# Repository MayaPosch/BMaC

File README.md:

# Building Monitoring and Control 

The Building Monitoring and Control (**BMaC**) system consists out multiple components which all work together to allow one to monitor and control conditions within a building.

Communication between these components is performed over MQTT, requiring the use of an (existing) MQTT broker. An Influx database instance is used to register sensor data, allowing this data to be used by other services. An existing InfluxDB instance can be used, or a new one created for the BMaC system.

A graphical overview:

## Components

* Command & Control server
* Command & Control client
* Control & Monitoring node
* AC control service
* OTA update service
* Influx-MQTT service

## Refactoring Notice ##

**Notice:** Be aware that the BMaC project is currently being refactored and will undergo a number of changes:

* ESP8266-based node firmware:
	- Auto-configuration using NyanSD service discovery.
	- Update & potentially remove unused modules.
* Merging of services:
	- The Command & Control server, AC & Influx-MQTT services are being merged into the 'Controller' service.
	- These old services will be retired after the merge completes.
* Web-based administration panel:
	- The new BMaC Controller server will provide a web-based interface for managing BMaC nodes and other parts of a BMaC installation.

### Command & Control server

This component (C&C server, or **CCS**) is used to register the configuration for individual nodes with. Each node can feature a different range of active sensors and actuators, which are enabled in the firmware at start-up of the node after they obtain their configuration from this server.

The C&C client is used to read out the current node configurations, update configurations and add new nodes.

### Command & Control client

This client (C&C client, or **CCC**) is based around a graphical user interface, which displays the map of the current building layout, along with the position of each node. By selecting a node, one can see its current configuration and update it.

After creating a new node or updating an existing one, the changed configuration can be saved on the C&C server or be sent directly to the node (useful for testing purposes).

### Control & Monitoring node

Also called **CMN**. In its current iteration these are ESP8266-based systems. Generally they are fitted into a wall- or ceiling-mounted enclosure using a custom board with the ability to mount temperature, CO2 and other sensors. They can also be in the form of a simple switch, in which case they are fitted into an electrical box, usually to replace a manual switch.

Each node runs the same firmware, yet can be configured via the CCS to only enable specific modules.

Current modules are:

* **Temperature/Humidity** - Uses the Bosch BME280 sensor to read temperature, humidity and air pressure.
* **CO2** - Uses the MH-Z19 and compatible (MH-Z14) CO2 sensor's serial interface to obtain PPM levels.
* **Jura** - Reads out current statistics on total number of coffee consumed for compatible Toptronic-based automatic coffee machines.
* **JuraTerm** - Allows for direct control of compatible Toptronic-based coffee machines using the serial protocol over MQTT.
* **Motion** - Uses compatible PIR motion sensors (e.g.  the HC-SR501) with 3.3V TTL output.
* **PWM** - Generates a PWM signal of variable duty, set to 1 KHz.
* **IO** - Uses the MCP23008 GPIO expander to increase the number of digital GPIO pins.
* **Switch** - Uses an external 2-coil latching relay to switch an input between two possible outputs and read the current setting back.

### AC control service

The AC control service (accontrol, or **ACCS**) builds upon the CCS, CMNs as well as the data stored in the Influx database in order to control the room temperature using installed Fan Coil Units (**FCUs**), along with the valves in the system (both 2- and 4-pipe FCUs).

It provides a HTTP REST API along with a simple browser-based interface using which one can set the target temperature for a particular node and read out the current temperature.

### OTA update service

The OTA update service (**OTAU**) works together with the CMN firmware to allow a CMN to update itself with a new firmware image. After the CMN receives an update trigger via its maintenance interface, it contacts a hard-coded HTTP URI to obtain the new firmware image.

The OTAU currently is a simple browser-based script using which CMNs can be added using their UID (MAC address) along with the name of the firmware image they should be downloading. When the CMN contacts the OTAU running inside a webserver, the OTAU selects the appropriate firmware image and sends it to the CMN.

### Influx-MQTT service

The Influx-MQTT service (**IMS**) can be configured to listen on a number of MQTT topics (sensor readings) and write those to a time series in the InfluxDB instance using its HTTP(S) line protocol.

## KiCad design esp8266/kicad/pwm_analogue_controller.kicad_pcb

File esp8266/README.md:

# Command & Control node

Also called **CMN**. In its current iteration these are ESP8266-based systems. Generally they are fitted into a wall- or ceiling-mounted enclosure using a custom board with the ability to mount temperature, CO2 and other sensors. They can also be in the form of a simple switch, in which case they are fitted into an electrical box, usually to replace a manual switch.

Each node runs the same firmware, yet can be configured via the CCS (Command & Control Server) to only enable specific modules.

Current modules are:

- **Temperature/Humidity** - Uses the Bosch BME280 sensor to read temperature, humidity and air pressure.
- **CO2** - Uses the MH-Z19 and compatible (MH-Z14) CO2 sensor's serial interface to obtain PPM levels.
- **Jura** - Reads out current statistics on total number of coffee consumed for compatible Toptronic-based automatic coffee machines.
- **JuraTerm** - Allows for direct control of compatible Toptronic-based coffee machines using the serial protocol over MQTT, terminal-style.
- **Motion** - Uses compatible PIR motion sensors (e.g.  the HC-SR501) with 3.3V TTL output.
- **PWM** - Generates a PWM signal of variable duty, set to 1 KHz.
- **IO** - Uses the MCP23008 GPIO expander to increase the number of digital GPIO pins.
- **Switch** - Uses an external 2-coil latching relay to switch an input between two possible outputs and read the current setting back.

## Usage ##

The firmware is designed to require minimal configuration. Other than the necessity of adding a file with the WiFi credentials (`files/wifi_creds.txt`), the configuration of the MQTT broker and OTA server is handled automatically, assuming the following dependencies are met:

- BMaC Controller server active on the network.
- MQTT broker active on the network.
- [NyanSD](https://github.com/MayaPosch/NyanSD "NyanSD") server running on port 11310 (UDP) for MQTT broker discovery.

With these services in place, the firmware will:

- Read the WiFi credentials from the `wifi_creds.txt` file.
- Connect to WiFi and broadcast a NyanSD message for the MQTT broker.
- Connect to the first MQTT broker.
- Send MQTT message to `cc/config` with its MAC as payload to obtain its configuration.

At this point the node should be active, and configurable via the BMaC Controller server.

## Building

This project is based on the Sming ESP8266 framework (https://github.com/SmingHub/Sming). As of writing the current 4.6 release is recommended.

After following the installation instructions for Sming in its documentation, to customise the BMaC firmware for the target WiFi network the credentials have to be added to the `files/` folder. This file has this format, with a question mark separating the SSID and password:

```
<WiFi SSID>?<WiFi password>
```

After this, there are a few more configuration options that can be set in the `component.mk` file of the project:

* Whether MQTT is run in secure (TLS) or insecure mode.

Note that when using TLS, one has to add the client certificate and key to the `files/` folder in binary format (not Base64):

* files/**esp8266.client.crt.binary**
* files/**esp8266.client.key.binary**

These files will then be added to the filesystem on the firmware image.

**NOTE:** Due to the limited RAM on the ESP8266, it is required to set the SSL fragment size option on the TLS termination point (MQTT broker or proxy, e.g. HAProxy). A fragment size of about 2 kB is recommended. The default 16 kB size (for TX & RX) will cause the ESP8266 to run out of memory during handshake and reset.

## PCB KiCad project ##

The KiCad project for the controller's PCB is found in the `kicad/` folder. From these the Gerber files can be generated for the PCBs.

The PCB is designed for the CamdenBoss CBRS01VWH enclosure (wall/ceiling-mount).

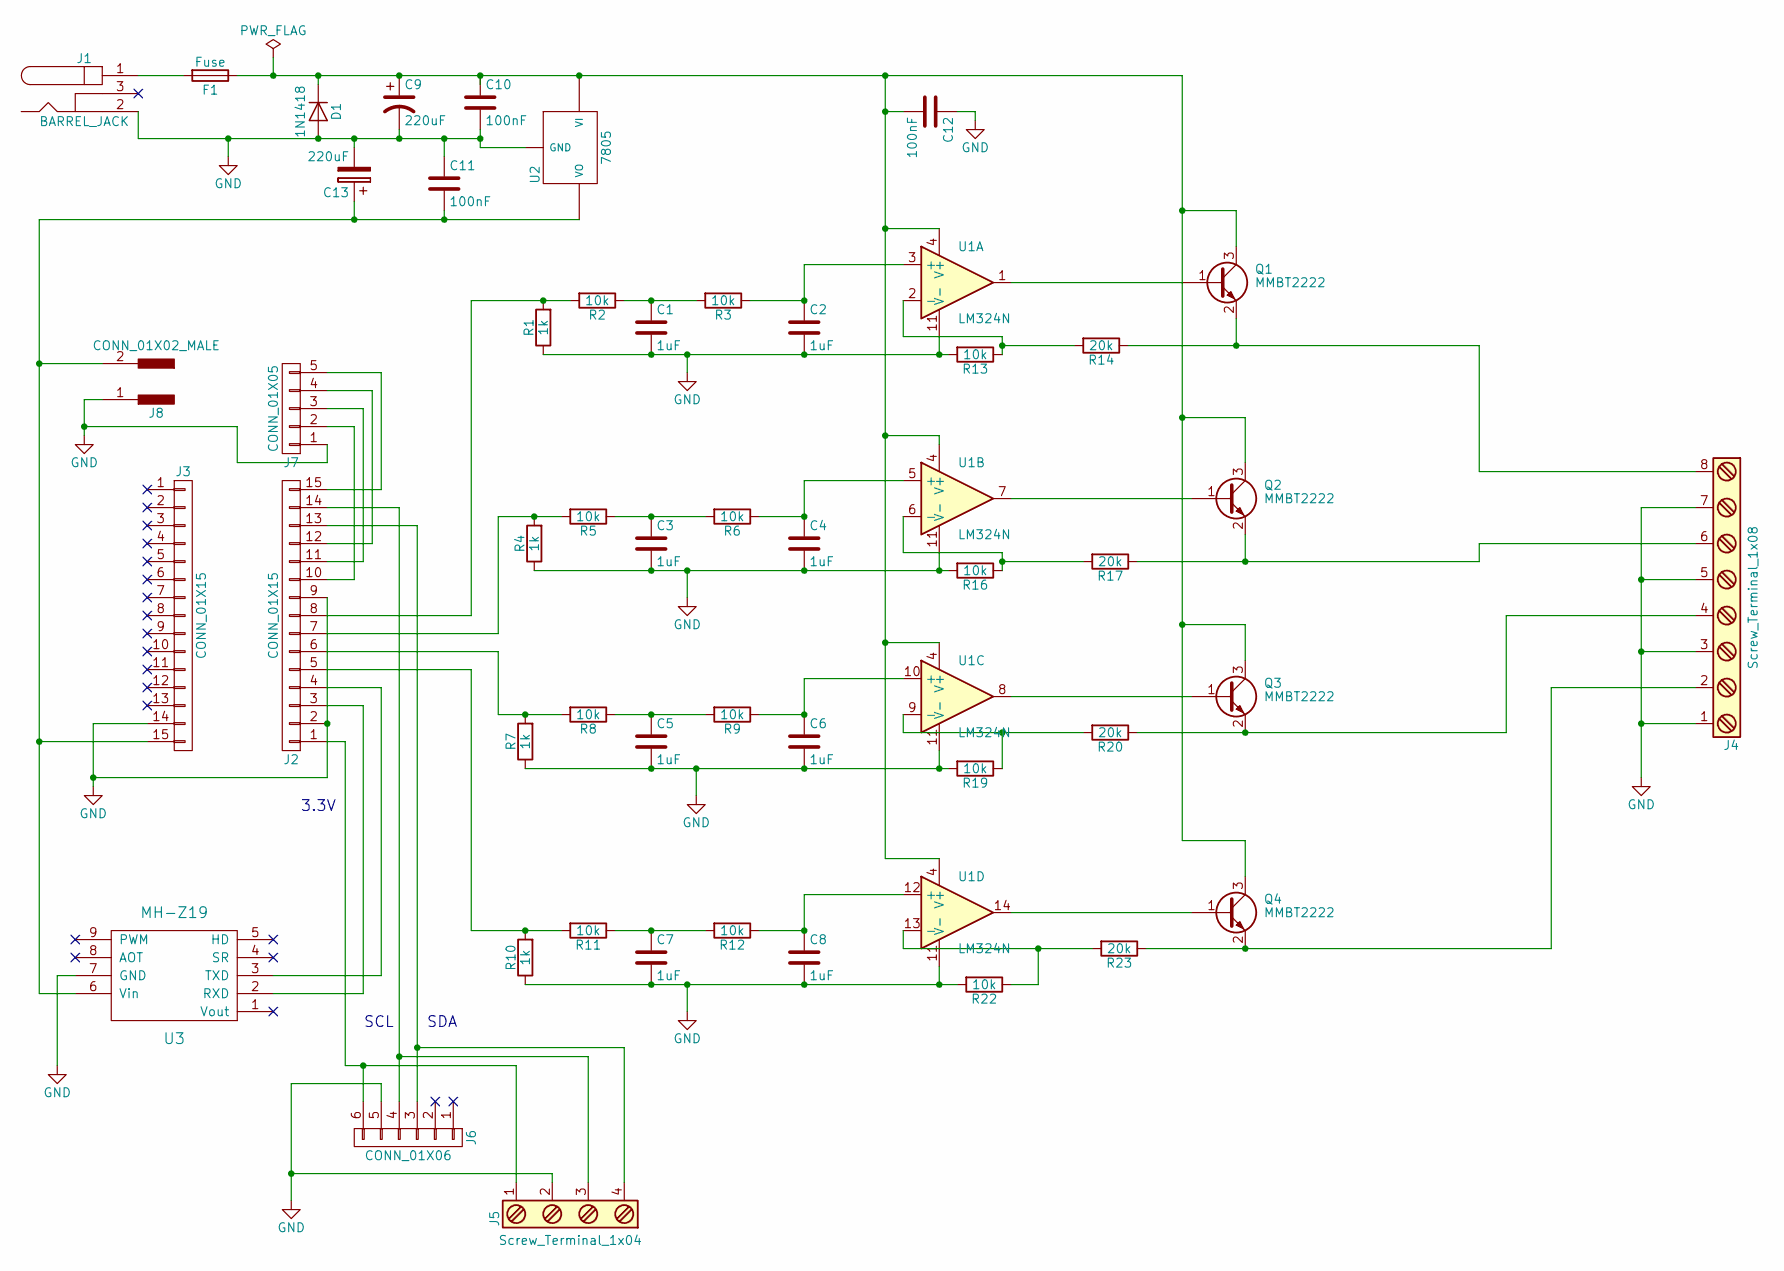
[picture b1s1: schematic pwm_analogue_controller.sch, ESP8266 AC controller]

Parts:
C1, C2, C3, C4, C5, C6, C7, C8: 1uF; C_0805_HandSoldering
C9, C13: 220uF; CP_Elec_10x10
C10, C11, C12: 100nF; C_0805_HandSoldering
D1: 1N1418; D_SOD-123
F1: Fuse; Fuse_SMD1206_HandSoldering
J1: BARREL_JACK; Pin_Header_Straight_1x02_Pitch2.54mm
J2, J3: CONN_01X15; Socket_Strip_Straight_1x15_Pitch2.54mm
J4: Screw_Terminal_1x08; TerminalBlock_Pheonix_MPT-2.54mm_8pol
J5: Screw_Terminal_1x04; TerminalBlock_Pheonix_MPT-2.54mm_4pol
J6: CONN_01X06; Socket_Strip_Straight_1x06_Pitch2.54mm
J7: CONN_01X05; Pin_Header_Straight_1x05_Pitch2.54mm
J8: CONN_01X02_MALE; Pin_Header_Straight_1x02_Pitch2.54mm
Q1, Q2, Q3, Q4: MMBT2222; SOT-23_Handsoldering
R1, R4, R7, R10: 1k; R_0805_HandSoldering
R2, R3, R5, R6, R8, R9, R11, R12, R13, R16, R19, R22: 10k; R_0805_HandSoldering
R14, R17, R20, R23: 20k; R_0805_HandSoldering
U1: LM324N; SOIC-14_3.9x8.7mm_Pitch1.27mm
U2: 7805; DCDC-Conv_RECOM_R-78E-0.5
U3: MH-Z19

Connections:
GND: C1.2, C2.2, C3.2, C4.2, C5.2, C6.2, C7.2, C8.2, C9.2, C10.2, C11.1, C12.1, C13.2, D1.2 (A), J1.2, J2.2, J2.9, J3.14, J4.1, J4.3, J4.5, J4.7, J5.2, J6.5, J7.1, J8.1, R1.1, R4.1, R7.1, R10.1, R13.2, R16.2, R19.2, R22.2, U1.11 (V-), U2.2 (GND), U3.7 (GND); also elsewhere on the board
unnamed: C1.1, R2.1, R3.2
unnamed: C2.1, R3.1, U1.3 (+)
unnamed: C3.1, R5.1, R6.2
unnamed: C4.1, R6.1, U1.5 (+)
unnamed: C5.1, R8.1, R9.2
unnamed: C6.1, R9.1, U1.10 (+)
unnamed: C7.1, R11.1, R12.2
unnamed: C8.1, R12.1, U1.12 (+)
unnamed 9: C9.1, C10.1, C12.2, D1.1 (K), F1.1, Q1.3 (C), Q2.3 (C), Q3.3 (C), Q4.3 (C), U1.4 (V+), U2.1 (VI); also elsewhere on the board
unnamed: C11.2, C13.1, J3.15, J8.2, U2.3 (VO), U3.6 (Vin)
unnamed: F1.2, J1.1
unnamed: J2.1, J5.1, J6.6
unnamed: J2.3, U3.2 (RXD)
unnamed: J2.4, U3.3 (TXD)
unnamed: J2.5, R10.2, R11.2
unnamed: J2.6, R7.2, R8.2
unnamed: J2.7, R4.2, R5.2
unnamed: J2.8, R1.2, R2.2
unnamed: J2.10, J7.2
unnamed: J2.11, J7.3
unnamed: J2.12, J7.4
unnamed: J2.13, J5.4, J6.3
unnamed: J2.14, J5.3, J6.4
unnamed: J2.15, J7.5
unnamed: J4.2, Q4.2 (E), R23.1
unnamed: J4.4, Q3.2 (E), R20.1
unnamed: J4.6, Q2.2 (E), R17.1
unnamed: J4.8, Q1.2 (E), R14.1
unnamed: Q1.1 (B), U1.1
unnamed: Q2.1 (B), U1.7
unnamed: Q3.1 (B), U1.8
unnamed: Q4.1 (B), U1.14
unnamed: R13.1, R14.2, U1.2 (-)
unnamed: R16.1, R17.2, U1.6 (-)
unnamed: R19.1, R20.2, U1.9 (-)
unnamed: R22.1, R23.2, U1.13 (-)

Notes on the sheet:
3.3V
SCL
SDA

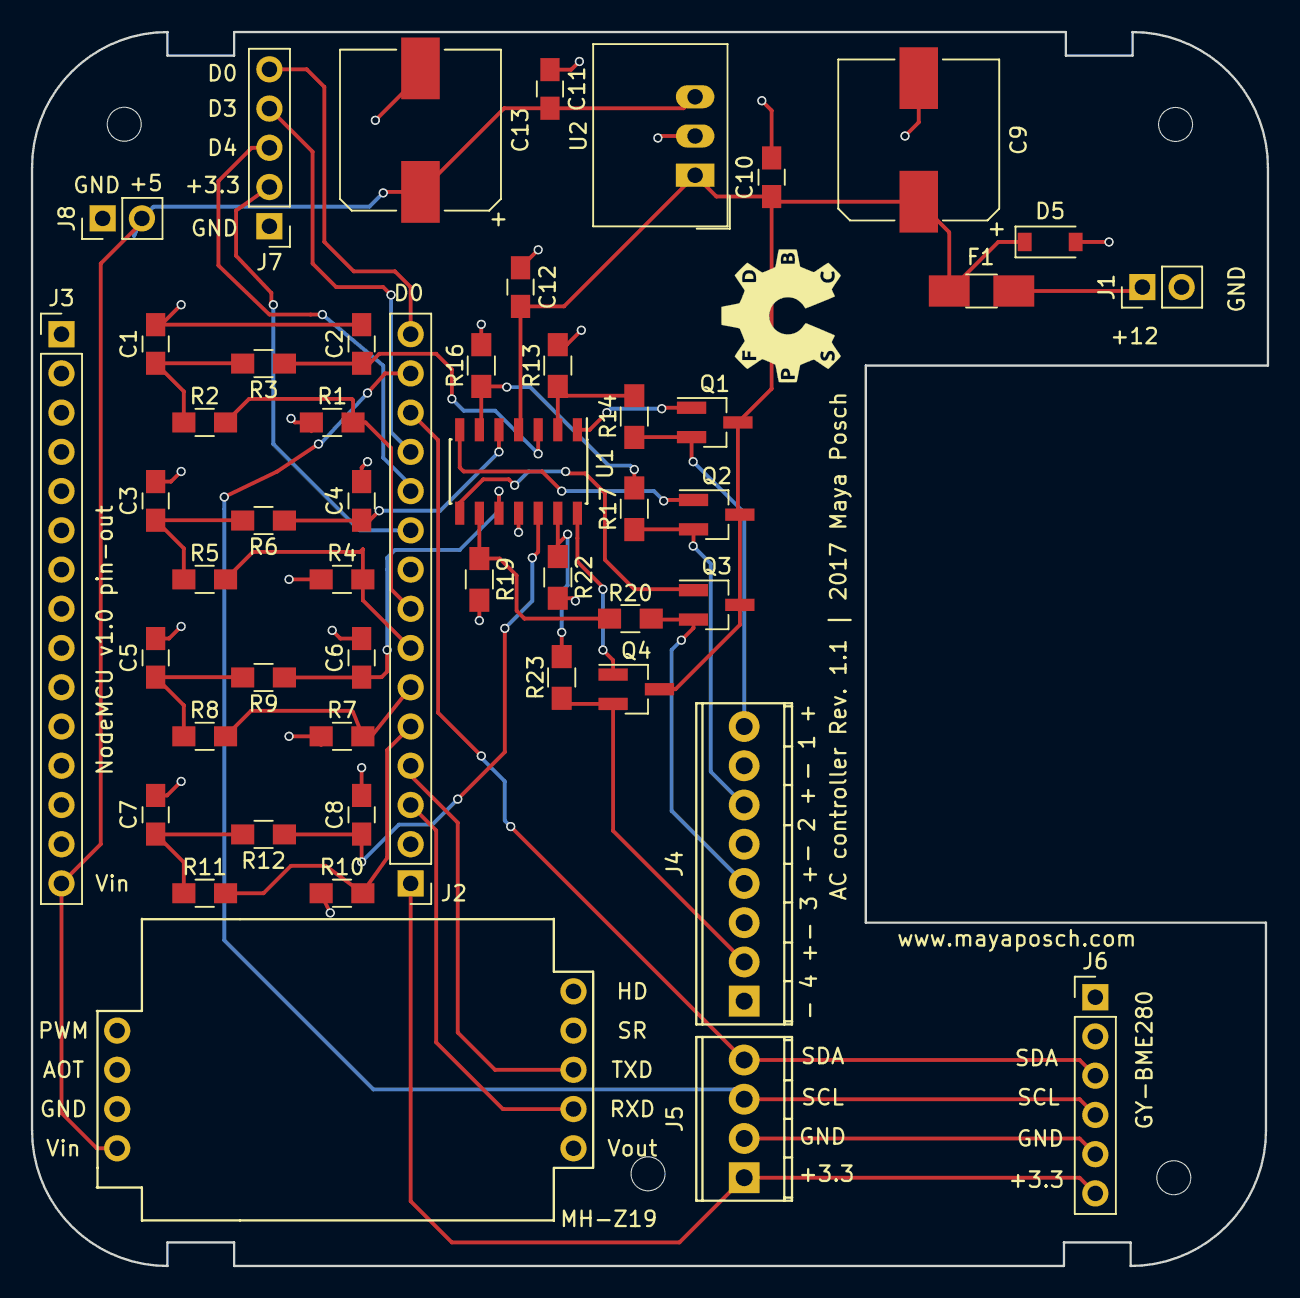
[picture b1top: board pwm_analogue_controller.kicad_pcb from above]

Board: 2 copper layers, 80.0 x 79.9 mm, 50 parts (0 on the bottom side), 37 nets.

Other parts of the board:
D5: D; D_SOD-123

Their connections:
GND: D5.2; also elsewhere on the board
unnamed 9: D5.1; also elsewhere on the board

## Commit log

2017-12-20 Initial commit.
2017-12-22 Add BMaC overview image. Add ESP8266 base firmware image.
2017-12-27 Fix sending of mimetype in the HTTP datahandler.
2017-12-27 [OTA] Add OTA update functionality to the C&C server.
    This uses HTTP for the delivery of images, and maintenance & configuration using MQTT.
2017-12-28 [OTA] Integrate dialogues for firmware imagine management into C&C client.
    Dialogues work, business logic for uploading images and node management still have to be implemented.
2017-12-28 [OTA] Fix behaviour of dialogues when using the default buttons to close the dialogue.
2018-02-27 Added AC controller KiCad project files.
2018-09-17 Refactored firmware, added plant module.
2018-11-18 Add skeleton for BMaC integration test building simulation.
2018-11-20 More integration test work. Some details still to be filled in.
2018-11-21 Finish SPI, I2C code skeletons in ESP mockup.
2018-11-22 Finish most connections between ESP firmware & simulation backend.
2018-11-23 More design changes to fit RPC model.
2018-11-25 Last design changes to simulation code before testing.
2018-11-26 Finished all but the Node & Device classes.
2018-11-27 Finish I2C and UART links in Node class.
2018-11-28 Refactoring phase 2.
2018-12-03 Add modified Libmosquitto library to the test. MinGW compatibility added.
2018-12-04 Finish integrating the Mosquitto client into the MQTT class.
2018-12-04 Add missing functions & reimplementations.
2018-12-04 Set up skeleton for device/room connection.
2018-12-05 Finalise I2C interface mock.
2018-12-06 Finish I2C interface with hardcoded BME280 sensor implementation.
2018-12-07 Start debugging simulation server.
2018-12-07 Made the integration server compile.
2018-12-08 Add Makefiles for server & FW sim. Partial debug of FW sim code.
2018-12-09 Finish UART implementation in sim server. Validate code compiles.
2018-12-10 Finish most of the FW sim debugging.
2018-12-11 Finalise all but Wiring classes.
2018-12-12 Refactor build system to make building firmware test binaries more elegant.
2018-12-12 Make simple firmware code compile and link successfully.
2018-12-13 Make more complex firmware compile & link.
2018-12-13 Add BME280 sensor library to testing framework.
2018-12-24 Update serial callback method in Jura module.
2018-12-25 Cleaning up the source code.
2019-02-05 Extend integration test to work with full firmware.
2019-02-06 Update client to work with current Libmosquitto version on Windows.
2019-03-23 Update integration test for current Sming develop branch. Fix NymphRPC issue in server.
2019-03-23 Update node integration test makefile.
2019-03-23 Update C&C server makefile to distinguish between Windows and other OSes.
2019-03-24 [TEST] Add signal handler to node's SmingCore main function.
2019-03-24 [TEST] Fix various small issues with test server.
2019-03-25 [TEST] Fix range of data handling issues.
2019-03-25 [TEST] Fix string split utility function in server.
2019-03-25 [TEST] Clean up code after changes.
2019-04-06 Update project for current development version of Sming.
2019-04-06 Integrate HX711 scale support with project.
2019-04-06 Change MQTT initialisation to before loading of modules.
2019-04-06 Update HX711 library, fix existing HX711 library.
2021-01-07 Update build system for current Sming version.
2021-01-07 Update application code for current Sming version.
2021-01-07 Update HX711 library: use local include for header.
2022-08-06 Commit initial version of the new BMaC Controller server.
2022-08-08 Test node rename & some tweaks. WIP.
2022-08-08 Add phony.
2022-08-08 Update folder name.
2022-08-08 Add RBoot stream.
2022-08-08 API update tweaks.
2022-08-08 Update to new API.
2022-08-28 Refactoring for services merge. Implement initial REST API.
2022-08-29 Implement WIP HTML/JS UI for node management. Add REST stub.
2022-08-29 Implement node update feature.
2022-08-29 Update node upon changed config.
2022-08-30 Add try/catch to node table query.
2022-09-01 Add node delete functionality to management UI & REST API.
2022-09-01 Fix DataHandler merge issues.
2022-09-01 Fix Nodes JSON & other small issues.
2022-09-01 Filter out null rows from nodes database.
2022-09-01 Fix JSON conversion, payload size, JSON parsing UI.
2022-09-01 Fix assigning of new node. Partially fix updating node.
2022-09-01 Fix reading out of node update JSON.
2022-09-01 Fix reading out of location on update.
2022-09-02 Fix node table insertion query. Fix update response.
2022-09-02 Move nodes after assigning. Check for duplicate UIDs.
2022-09-02 Add WIP Controller commissioning protocol.
2022-09-02 Fix row insert location & row removal.
2022-09-03 Integrate NyanSD client, read WiFi credentials from SPIFFS.
2022-09-04 Update app to use OtaManager.
2022-09-05 Add second SPIFFS partition to hardware config
2022-09-05 Add `libs` to Component search path
    No need to copy libs
2022-09-05 Get SPIFFS slot from OtaManager
2022-09-05 Redirect Host debug output from UART1 to console
2022-09-05 Check for valid SPIFFS partition found.
2022-09-05 Fix reading out WiFi credentials file.
2022-09-05 Update firmware readme.
2022-09-08 Add refactoring notice to main README.
2022-09-08 Refactor Influx functionality into dedicated class.
2022-09-08 Update existing assigned node on update.
2022-09-15 Add monitoring topics.
2022-09-15 Fix adding of monitoring topics.
2022-09-18 Enable DHT22 as fallback if no BME280.
2022-09-18 Fixes after NyanSD integration.
2022-09-18 Tweak CO2 module, add more debug output.
2022-10-03 Reduce logging level to Warning.
2022-12-03 Fix cast overview with unsigned type.
2022-12-03 Change error reporting.
2023-02-02 Add Systemd & OpenRC service files for BMaC controller.
2023-02-02 Correct product variable name.
2023-02-02 Add architecture sub-folder.
2023-02-02 Make htdocs path configurable.
